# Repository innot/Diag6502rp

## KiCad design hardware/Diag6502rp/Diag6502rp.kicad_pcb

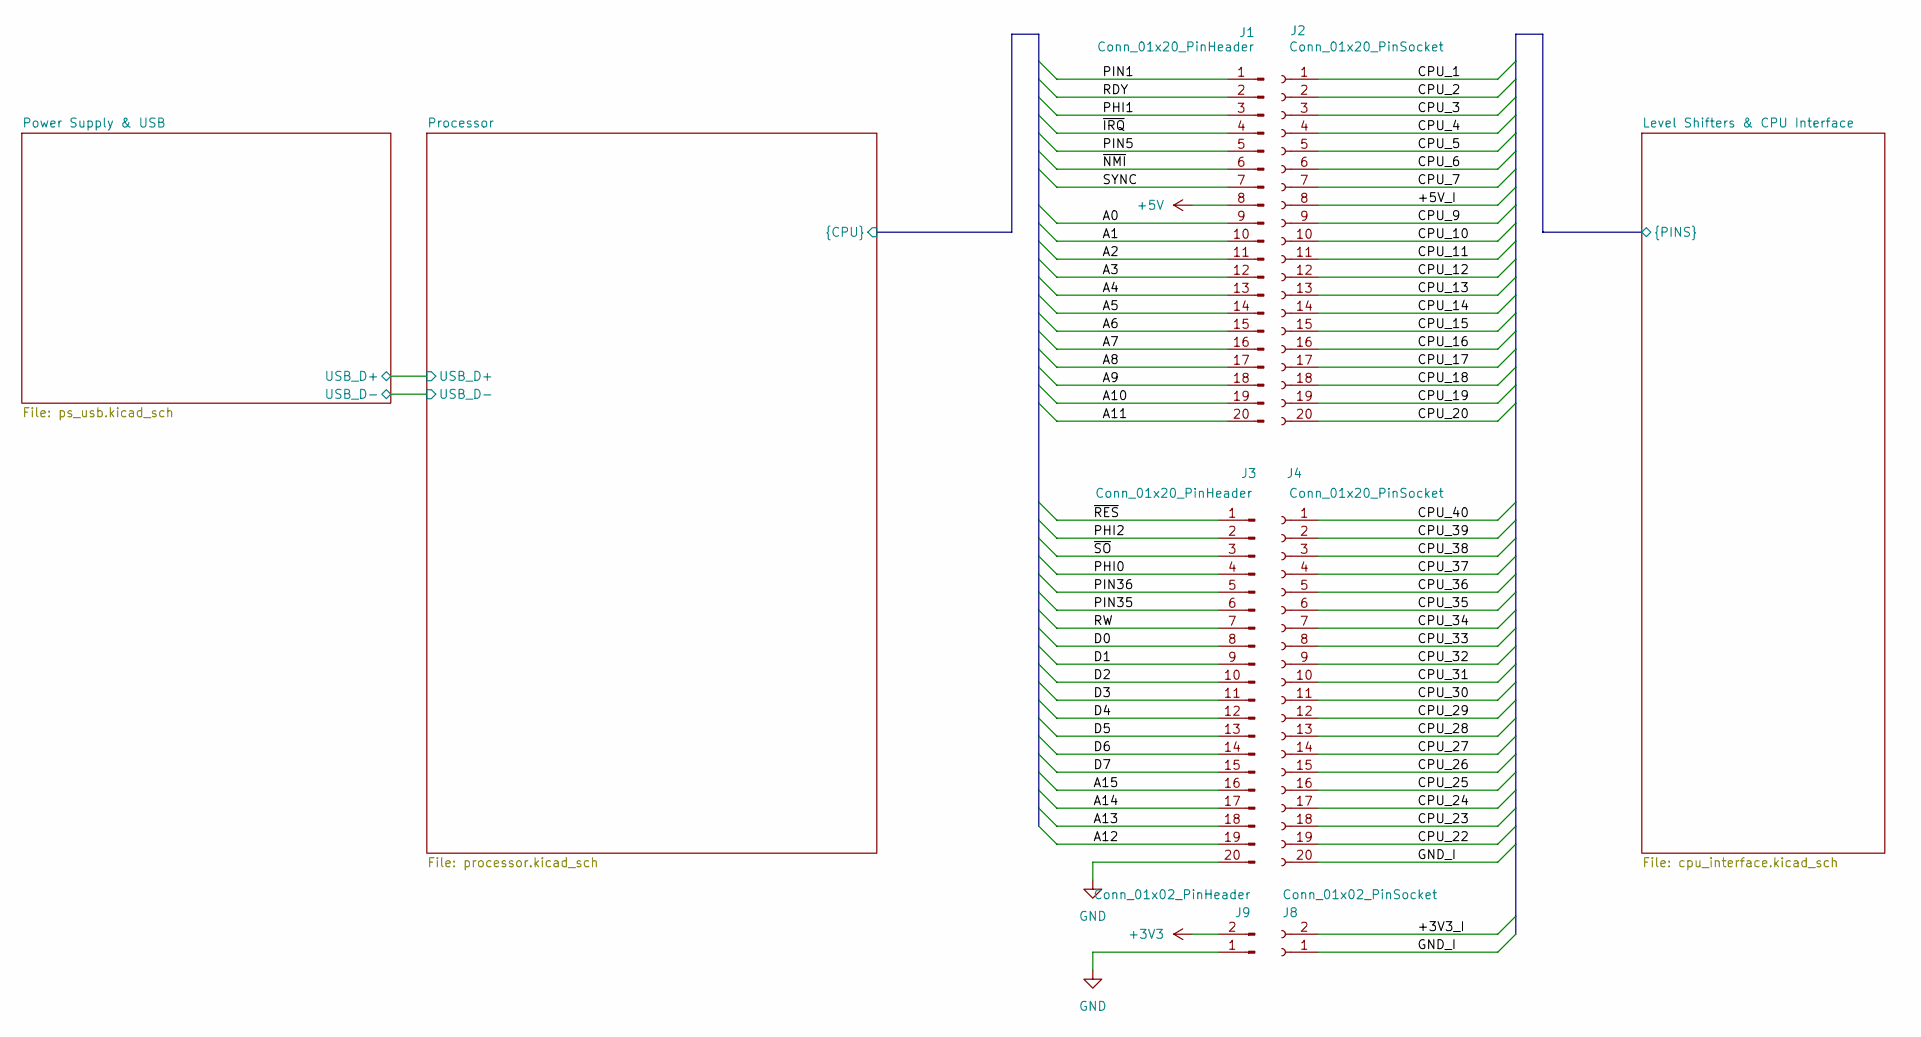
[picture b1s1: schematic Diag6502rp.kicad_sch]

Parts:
J1, J3: Conn_01x20_PinHeader; PinHeader_1x20_P2.54mm_Vertical; LCSC Part # C50981
J2, J4: Conn_01x20_PinSocket; PinSocket_1x20_P2.54mm_Vertical; LCSC Part # C7499336
J8: Conn_01x02_PinSocket; PinSocket_1x02_P2.54mm_Vertical; LCSC Part # C7499322
J9: Conn_01x02_PinHeader; PinHeader_1x02_P2.54mm_Vertical; LCSC Part # C492401

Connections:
+3V3: J9.2; also elsewhere on the board
+5V: J1.8; also elsewhere on the board
/Level Shifters & CPU Interface/+3V3_I: J8.2; also elsewhere on the board
/Level Shifters & CPU Interface/+5V_I: J2.8; also elsewhere on the board
/Level Shifters & CPU Interface/CPU_1: J2.1; also elsewhere on the board
/Level Shifters & CPU Interface/CPU_2: J2.2; also elsewhere on the board
/Level Shifters & CPU Interface/CPU_3: J2.3; also elsewhere on the board
/Level Shifters & CPU Interface/CPU_4: J2.4; also elsewhere on the board
/Level Shifters & CPU Interface/CPU_5: J2.5; also elsewhere on the board
/Level Shifters & CPU Interface/CPU_6: J2.6; also elsewhere on the board
/Level Shifters & CPU Interface/CPU_7: J2.7; also elsewhere on the board
/Level Shifters & CPU Interface/CPU_9: J2.9; also elsewhere on the board
/Level Shifters & CPU Interface/CPU_10: J2.10; also elsewhere on the board
/Level Shifters & CPU Interface/CPU_11: J2.11; also elsewhere on the board
/Level Shifters & CPU Interface/CPU_12: J2.12; also elsewhere on the board
/Level Shifters & CPU Interface/CPU_13: J2.13; also elsewhere on the board
/Level Shifters & CPU Interface/CPU_14: J2.14; also elsewhere on the board
/Level Shifters & CPU Interface/CPU_15: J2.15; also elsewhere on the board
/Level Shifters & CPU Interface/CPU_16: J2.16; also elsewhere on the board
/Level Shifters & CPU Interface/CPU_17: J2.17; also elsewhere on the board
/Level Shifters & CPU Interface/CPU_18: J2.18; also elsewhere on the board
/Level Shifters & CPU Interface/CPU_19: J2.19; also elsewhere on the board
/Level Shifters & CPU Interface/CPU_20: J2.20; also elsewhere on the board
/Level Shifters & CPU Interface/CPU_22: J4.19; also elsewhere on the board
/Level Shifters & CPU Interface/CPU_23: J4.18; also elsewhere on the board
/Level Shifters & CPU Interface/CPU_24: J4.17; also elsewhere on the board
/Level Shifters & CPU Interface/CPU_25: J4.16; also elsewhere on the board
/Level Shifters & CPU Interface/CPU_26: J4.15; also elsewhere on the board
/Level Shifters & CPU Interface/CPU_27: J4.14; also elsewhere on the board
/Level Shifters & CPU Interface/CPU_28: J4.13; also elsewhere on the board
/Level Shifters & CPU Interface/CPU_29: J4.12; also elsewhere on the board
/Level Shifters & CPU Interface/CPU_30: J4.11; also elsewhere on the board
/Level Shifters & CPU Interface/CPU_31: J4.10; also elsewhere on the board
/Level Shifters & CPU Interface/CPU_32: J4.9; also elsewhere on the board
/Level Shifters & CPU Interface/CPU_33: J4.8; also elsewhere on the board
/Level Shifters & CPU Interface/CPU_34: J4.7; also elsewhere on the board
/Level Shifters & CPU Interface/CPU_35: J4.6; also elsewhere on the board
/Level Shifters & CPU Interface/CPU_36: J4.5; also elsewhere on the board
/Level Shifters & CPU Interface/CPU_37: J4.4; also elsewhere on the board
/Level Shifters & CPU Interface/CPU_38: J4.3; also elsewhere on the board
/Level Shifters & CPU Interface/CPU_39: J4.2; also elsewhere on the board
/Level Shifters & CPU Interface/CPU_40: J4.1; also elsewhere on the board
/Level Shifters & CPU Interface/GND_I: J4.20, J8.1; also elsewhere on the board
/Processor/A0: J1.9; also elsewhere on the board
/Processor/A1: J1.10; also elsewhere on the board
/Processor/A2: J1.11; also elsewhere on the board
/Processor/A3: J1.12; also elsewhere on the board
/Processor/A4: J1.13; also elsewhere on the board
/Processor/A5: J1.14; also elsewhere on the board
/Processor/A6: J1.15; also elsewhere on the board
/Processor/A7: J1.16; also elsewhere on the board
/Processor/A8: J1.17; also elsewhere on the board
/Processor/A9: J1.18; also elsewhere on the board
/Processor/A10: J1.19; also elsewhere on the board
/Processor/A11: J1.20; also elsewhere on the board
/Processor/A12: J3.19; also elsewhere on the board
/Processor/A13: J3.18; also elsewhere on the board
/Processor/A14: J3.17; also elsewhere on the board
/Processor/A15: J3.16; also elsewhere on the board
/Processor/D0: J3.8; also elsewhere on the board
/Processor/D1: J3.9; also elsewhere on the board
/Processor/D2: J3.10; also elsewhere on the board
/Processor/D3: J3.11; also elsewhere on the board
/Processor/D4: J3.12; also elsewhere on the board
/Processor/D5: J3.13; also elsewhere on the board
/Processor/D6: J3.14; also elsewhere on the board
/Processor/D7: J3.15; also elsewhere on the board
/Processor/PHI0: J3.4; also elsewhere on the board
/Processor/PHI1: J1.3; also elsewhere on the board
/Processor/PHI2: J3.2; also elsewhere on the board
/Processor/PIN1: J1.1; also elsewhere on the board
/Processor/PIN5: J1.5; also elsewhere on the board
/Processor/PIN35: J3.6; also elsewhere on the board
/Processor/PIN36: J3.5; also elsewhere on the board
/Processor/RDY: J1.2; also elsewhere on the board
/Processor/RW: J3.7; also elsewhere on the board
/Processor/SYNC: J1.7; also elsewhere on the board
/Processor/~IRQ: J1.4; also elsewhere on the board
/Processor/~NMI: J1.6; also elsewhere on the board
/Processor/~RES: J3.1; also elsewhere on the board
/Processor/~SO: J3.3; also elsewhere on the board
GND: J3.20, J9.1; also elsewhere on the board

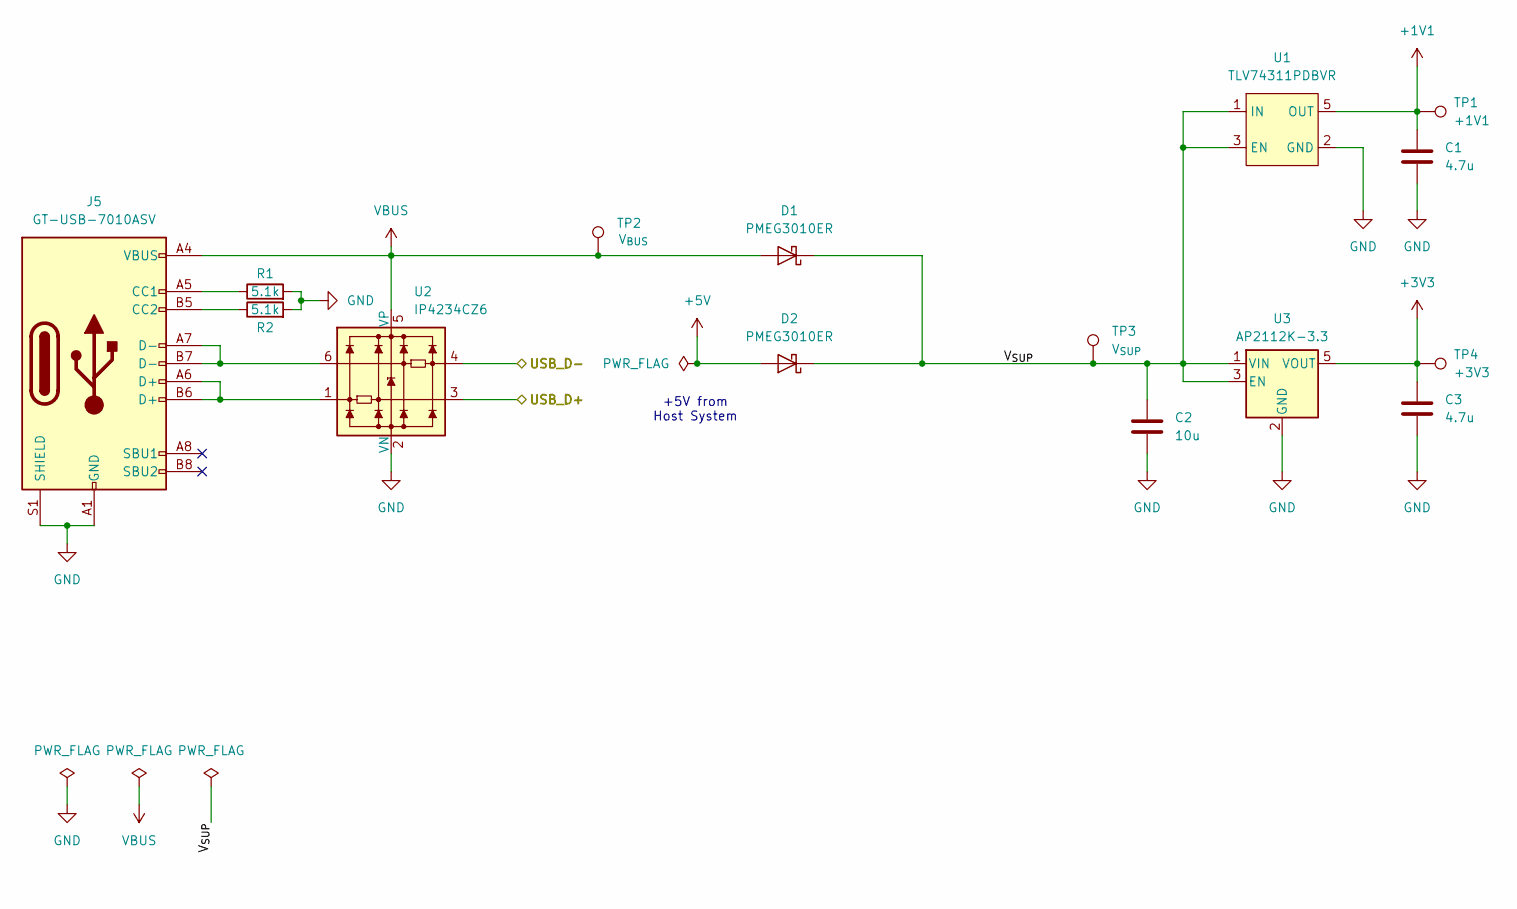
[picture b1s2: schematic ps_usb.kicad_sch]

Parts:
C1, C3: 4.7u; C_0402_1005Metric; LCSC Part # C23733
C2: 10u; C_0603_1608Metric; LCSC Part # C19702
D1, D2: PMEG3010ER; Nexperia_CFP3_SOD-123W; LCSC Part # C456106
J5: GT-USB-7010ASV; USB_C_Receptacle_G-Switch_GT-USB-7010ASV
R1, R2: 5.1k; R_0402_1005Metric; LCSC Part # C25905
TP1: +1V1; TestPoint_Pad_1.0x1.0mm
TP2: V_{BUS}; TestPoint_Pad_1.0x1.0mm
TP3: V_{SUP}; TestPoint_Pad_1.0x1.0mm
TP4: +3V3; TestPoint_Pad_1.0x1.0mm
U1: TLV74311PDBVR; SOT-23-5; LCSC Part # C485147
U2: IP4234CZ6; SC-74-6_1.55x2.9mm_P0.95mm; LCSC Part # C455086
U3: AP2112K-3.3; SOT-23-5; LCSC Part # C51118

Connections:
+1V1: C1.1, TP1.1, U1.5 (OUT); also elsewhere on the board
+3V3: C3.1, TP4.1, U3.5 (VOUT); also elsewhere on the board
+5V: D2.2 (A); also elsewhere on the board
/Power Supply & USB/V_{SUP}: C2.1, D1.1 (K), D2.1 (K), TP3.1, U1.1 (IN), U1.3 (EN), U3.1 (VIN), U3.3 (EN)
/Processor/USB_D+: U2.3; also elsewhere on the board
/Processor/USB_D-: U2.4; also elsewhere on the board
GND: C1.2, C2.2, C3.2, J5.A1 (GND), J5.A12 (GND), J5.B1 (GND), J5.B12 (GND), J5.S1 (SHIELD), R1.2, R2.2, U1.2 (GND), U2.2 (VN), U3.2 (GND); also elsewhere on the board
unnamed: J5.A5 (CC1), R1.1
unnamed: J5.B5 (CC2), R2.1
unnamed: J5.A6 (D+), J5.B6 (D+), U2.1
unnamed: J5.A7 (D-), J5.B7 (D-), U2.6
VBUS: D1.2 (A), J5.A4 (VBUS), J5.A9 (VBUS), J5.B4 (VBUS), J5.B9 (VBUS), TP2.1, U2.5 (VP)

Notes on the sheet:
+5V from Host System

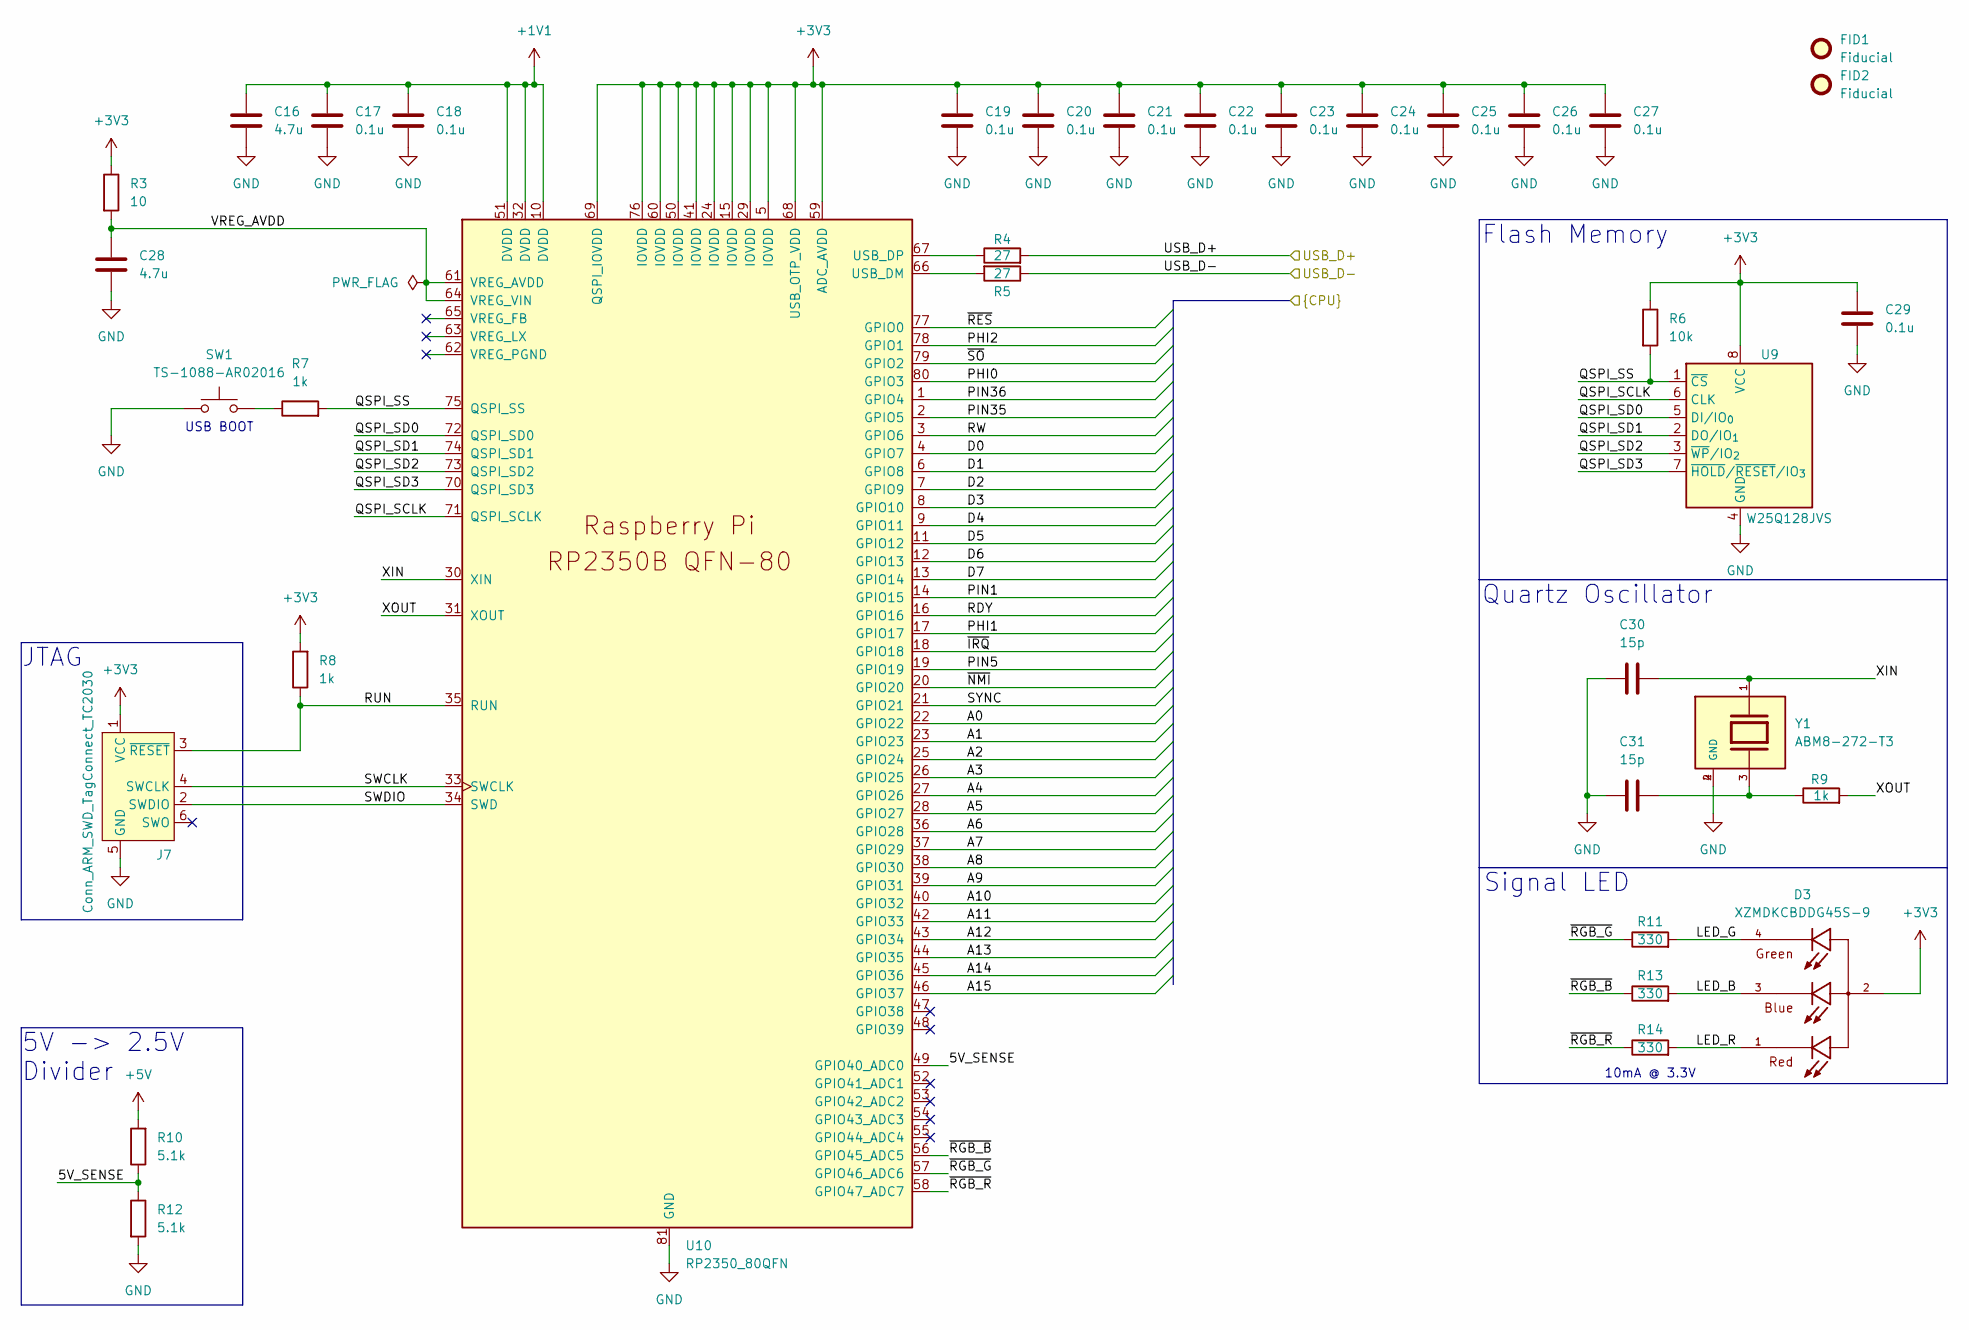
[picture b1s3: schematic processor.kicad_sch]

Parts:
C16, C28: 4.7u; C_0402_1005Metric; LCSC Part # C23733
C17, C18, C19, C20, C21, C22, C23, C24, C25, C26, C27, C29: 0.1u; C_0402_1005Metric; LCSC Part # C1525
C30, C31: 15p; C_0402_1005Metric; LCSC Part # C1548
D3: XZMDKCBDDG45S-9; LED_XZMDKCBDDG45S-9; PARTREV V11-Z; DigiKey_Part_Number 1497-1257-2-ND
FID1, FID2: Fiducial; Fiducial_1mm_Mask2mm
J7: Conn_ARM_SWD_TagConnect_TC2030; Tag-Connect_TC2030-IDC-FP_2x03_P1.27mm_Vertical
R3: 10; R_0402_1005Metric; LCSC Part # C25077
R4, R5: 27; R_0402_1005Metric; LCSC Part # C138021
R6: 10k; R_0402_1005Metric; LCSC Part # C25744
R7, R8, R9: 1k; R_0402_1005Metric; LCSC Part # C11702
R10, R12: 5.1k; R_0402_1005Metric; LCSC Part # C25905
R11, R13, R14: 330; R_0402_1005Metric; LCSC Part # C25130
SW1: TS-1088-AR02016; TS-1088-xxxxxxx; LCSC Part # C720477
U9: W25Q128JVS; SOIC-8_5.3x5.3mm_P1.27mm; LCSC Part # C97521
U10: RP2350_80QFN; RP2350-QFN-80-1EP_10x10_P0.4mm_EP3.4x3.4mm_ThermalVias; LCSC Part # C42415655
Y1: ABM8-272-T3; XTAL_ABM8-272-T3; PARTREV 07-29-20; LCSC Part # C20625731

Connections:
+1V1: C16.1, C17.1, C18.1, U10.10 (DVDD), U10.32 (DVDD), U10.51 (DVDD); also elsewhere on the board
+3V3: C19.1, C20.1, C21.1, C22.1, C23.1, C24.1, C25.1, C26.1, C27.1, C29.1, D3.2, J7.1 (VCC), R3.1, R6.1, R8.2, U9.8 (VCC), U10.5 (IOVDD), U10.15 (IOVDD), U10.24 (IOVDD), U10.29 (IOVDD), U10.41 (IOVDD), U10.50 (IOVDD), U10.59 (ADC_AVDD), U10.60 (IOVDD), U10.68 (USB_OTP_VDD), U10.69 (QSPI_IOVDD), U10.76 (IOVDD); also elsewhere on the board
+5V: R10.2; also elsewhere on the board
/Processor/5V_SENSE: R10.1, R12.1, U10.49 (GPIO40_ADC0)
/Processor/A0: U10.22 (GPIO22); also elsewhere on the board
/Processor/A1: U10.23 (GPIO23); also elsewhere on the board
/Processor/A2: U10.25 (GPIO24); also elsewhere on the board
/Processor/A3: U10.26 (GPIO25); also elsewhere on the board
/Processor/A4: U10.27 (GPIO26); also elsewhere on the board
/Processor/A5: U10.28 (GPIO27); also elsewhere on the board
/Processor/A6: U10.36 (GPIO28); also elsewhere on the board
/Processor/A7: U10.37 (GPIO29); also elsewhere on the board
/Processor/A8: U10.38 (GPIO30); also elsewhere on the board
/Processor/A9: U10.39 (GPIO31); also elsewhere on the board
/Processor/A10: U10.40 (GPIO32); also elsewhere on the board
/Processor/A11: U10.42 (GPIO33); also elsewhere on the board
/Processor/A12: U10.43 (GPIO34); also elsewhere on the board
/Processor/A13: U10.44 (GPIO35); also elsewhere on the board
/Processor/A14: U10.45 (GPIO36); also elsewhere on the board
/Processor/A15: U10.46 (GPIO37); also elsewhere on the board
/Processor/D0: U10.4 (GPIO7); also elsewhere on the board
/Processor/D1: U10.6 (GPIO8); also elsewhere on the board
/Processor/D2: U10.7 (GPIO9); also elsewhere on the board
/Processor/D3: U10.8 (GPIO10); also elsewhere on the board
/Processor/D4: U10.9 (GPIO11); also elsewhere on the board
/Processor/D5: U10.11 (GPIO12); also elsewhere on the board
/Processor/D6: U10.12 (GPIO13); also elsewhere on the board
/Processor/D7: U10.13 (GPIO14); also elsewhere on the board
/Processor/LED_B: D3.3, R13.2
/Processor/LED_G: D3.4, R11.2
/Processor/LED_R: D3.1, R14.2
/Processor/PHI0: U10.80 (GPIO3); also elsewhere on the board
/Processor/PHI1: U10.17 (GPIO17); also elsewhere on the board
/Processor/PHI2: U10.78 (GPIO1); also elsewhere on the board
/Processor/PIN1: U10.14 (GPIO15); also elsewhere on the board
/Processor/PIN5: U10.19 (GPIO19); also elsewhere on the board
/Processor/PIN35: U10.2 (GPIO5); also elsewhere on the board
/Processor/PIN36: U10.1 (GPIO4); also elsewhere on the board
/Processor/QSPI_SCLK: U9.6 (CLK), U10.71 (QSPI_SCLK)
/Processor/QSPI_SD0: U9.5 (DI/IO_{0}), U10.72 (QSPI_SD0)
/Processor/QSPI_SD1: U9.2 (DO/IO_{1}), U10.74 (QSPI_SD1)
/Processor/QSPI_SD2: U9.3 (~WP/IO_{2}), U10.73 (QSPI_SD2)
/Processor/QSPI_SD3: U9.7 (~HOLD/~RESET/IO_{3}), U10.70 (QSPI_SD3)
/Processor/QSPI_SS: R6.2, R7.2, U9.1 (~CS), U10.75 (QSPI_SS)
/Processor/RDY: U10.16 (GPIO16); also elsewhere on the board
/Processor/RUN: J7.3 (~RESET), R8.1, U10.35 (RUN)
/Processor/RW: U10.3 (GPIO6); also elsewhere on the board
/Processor/SWCLK: J7.4 (SWCLK), U10.33 (SWCLK)
/Processor/SWDIO: J7.2 (SWDIO), U10.34 (SWD)
/Processor/SYNC: U10.21 (GPIO21); also elsewhere on the board
/Processor/USB_D+: R4.2; also elsewhere on the board
/Processor/USB_D-: R5.1; also elsewhere on the board
/Processor/VREG_AVDD: C28.1, R3.2, U10.61 (VREG_AVDD), U10.64 (VREG_VIN)
/Processor/XIN: C30.2, U10.30 (XIN), Y1.1
/Processor/XOUT: R9.2, U10.31 (XOUT)
/Processor/~IRQ: U10.18 (GPIO18); also elsewhere on the board
/Processor/~NMI: U10.20 (GPIO20); also elsewhere on the board
/Processor/~RES: U10.77 (GPIO0); also elsewhere on the board
/Processor/~RGB_B: R13.1, U10.56 (GPIO45_ADC5)
/Processor/~RGB_G: R11.1, U10.57 (GPIO46_ADC6)
/Processor/~RGB_R: R14.1, U10.58 (GPIO47_ADC7)
/Processor/~SO: U10.79 (GPIO2); also elsewhere on the board
GND: C16.2, C17.2, C18.2, C19.2, C20.2, C21.2, C22.2, C23.2, C24.2, C25.2, C26.2, C27.2, C28.2, C29.2, C30.1, C31.1, J7.5 (GND), R12.2, SW1.1, U9.4 (GND), U10.81 (GND), Y1.2 (GND), Y1.4 (GND); also elsewhere on the board
unnamed: C31.2, R9.1, Y1.3
unnamed: R7.1, SW1.2
unnamed: R5.2, U10.66 (USB_DM)
unnamed: R4.1, U10.67 (USB_DP)

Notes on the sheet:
10mA @ 3.3V
5V -> 2.5V Divider
USB BOOT
Signal LED
JTAG
Quartz Oscillator
Flash Memory

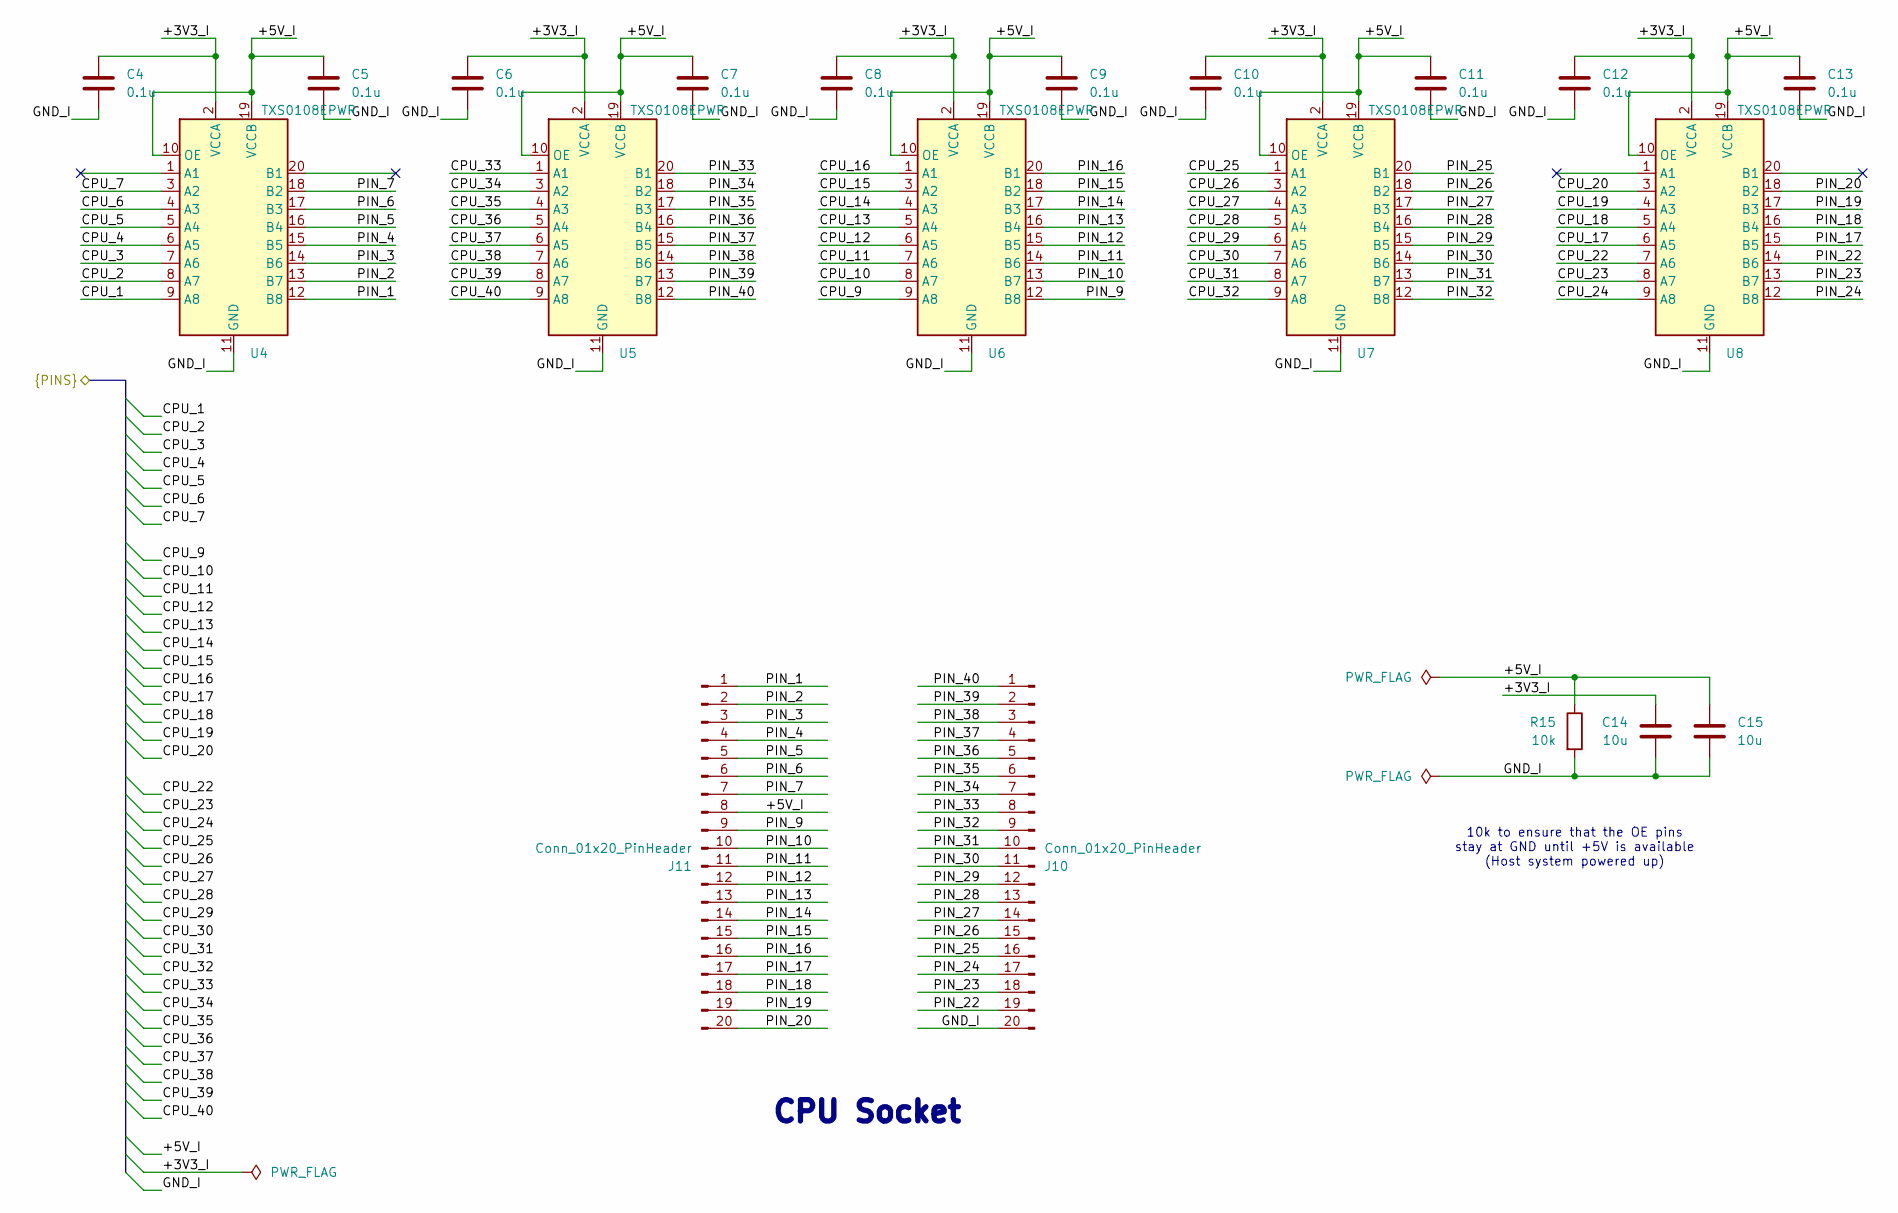
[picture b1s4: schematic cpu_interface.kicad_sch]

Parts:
C4, C5, C6, C7, C8, C9, C10, C11, C12, C13: 0.1u; C_0402_1005Metric; LCSC Part # C1525
C14, C15: 10u; C_0603_1608Metric; LCSC Part # C19702
J10, J11: Conn_01x20_PinHeader; PinHeader_1x20_P2.54mm_Vertical; LCSC Part # C50981
R15: 10k; R_0402_1005Metric; LCSC Part # C25744
U4, U5, U6, U7, U8: TXS0108EPWR; TSSOP-20_4.4x6.5mm_P0.65mm; LCSC Part # C17206

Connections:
/Level Shifters & CPU Interface/+3V3_I: C4.1, C6.1, C8.1, C10.1, C12.1, C14.1, U4.2 (VCCA), U5.2 (VCCA), U6.2 (VCCA), U7.2 (VCCA), U8.2 (VCCA); also elsewhere on the board
/Level Shifters & CPU Interface/+5V_I: C5.1, C7.1, C9.1, C11.1, C13.1, C15.1, J11.8, R15.1, U4.10 (OE), U4.19 (VCCB), U5.10 (OE), U5.19 (VCCB), U6.10 (OE), U6.19 (VCCB), U7.10 (OE), U7.19 (VCCB), U8.10 (OE), U8.19 (VCCB); also elsewhere on the board
/Level Shifters & CPU Interface/CPU_1: U4.9 (A8); also elsewhere on the board
/Level Shifters & CPU Interface/CPU_2: U4.8 (A7); also elsewhere on the board
/Level Shifters & CPU Interface/CPU_3: U4.7 (A6); also elsewhere on the board
/Level Shifters & CPU Interface/CPU_4: U4.6 (A5); also elsewhere on the board
/Level Shifters & CPU Interface/CPU_5: U4.5 (A4); also elsewhere on the board
/Level Shifters & CPU Interface/CPU_6: U4.4 (A3); also elsewhere on the board
/Level Shifters & CPU Interface/CPU_7: U4.3 (A2); also elsewhere on the board
/Level Shifters & CPU Interface/CPU_9: U6.9 (A8); also elsewhere on the board
/Level Shifters & CPU Interface/CPU_10: U6.8 (A7); also elsewhere on the board
/Level Shifters & CPU Interface/CPU_11: U6.7 (A6); also elsewhere on the board
/Level Shifters & CPU Interface/CPU_12: U6.6 (A5); also elsewhere on the board
/Level Shifters & CPU Interface/CPU_13: U6.5 (A4); also elsewhere on the board
/Level Shifters & CPU Interface/CPU_14: U6.4 (A3); also elsewhere on the board
/Level Shifters & CPU Interface/CPU_15: U6.3 (A2); also elsewhere on the board
/Level Shifters & CPU Interface/CPU_16: U6.1 (A1); also elsewhere on the board
/Level Shifters & CPU Interface/CPU_17: U8.6 (A5); also elsewhere on the board
/Level Shifters & CPU Interface/CPU_18: U8.5 (A4); also elsewhere on the board
/Level Shifters & CPU Interface/CPU_19: U8.4 (A3); also elsewhere on the board
/Level Shifters & CPU Interface/CPU_20: U8.3 (A2); also elsewhere on the board
/Level Shifters & CPU Interface/CPU_22: U8.7 (A6); also elsewhere on the board
/Level Shifters & CPU Interface/CPU_23: U8.8 (A7); also elsewhere on the board
/Level Shifters & CPU Interface/CPU_24: U8.9 (A8); also elsewhere on the board
/Level Shifters & CPU Interface/CPU_25: U7.1 (A1); also elsewhere on the board
/Level Shifters & CPU Interface/CPU_26: U7.3 (A2); also elsewhere on the board
/Level Shifters & CPU Interface/CPU_27: U7.4 (A3); also elsewhere on the board
/Level Shifters & CPU Interface/CPU_28: U7.5 (A4); also elsewhere on the board
/Level Shifters & CPU Interface/CPU_29: U7.6 (A5); also elsewhere on the board
/Level Shifters & CPU Interface/CPU_30: U7.7 (A6); also elsewhere on the board
/Level Shifters & CPU Interface/CPU_31: U7.8 (A7); also elsewhere on the board
/Level Shifters & CPU Interface/CPU_32: U7.9 (A8); also elsewhere on the board
/Level Shifters & CPU Interface/CPU_33: U5.1 (A1); also elsewhere on the board
/Level Shifters & CPU Interface/CPU_34: U5.3 (A2); also elsewhere on the board
/Level Shifters & CPU Interface/CPU_35: U5.4 (A3); also elsewhere on the board
/Level Shifters & CPU Interface/CPU_36: U5.5 (A4); also elsewhere on the board
/Level Shifters & CPU Interface/CPU_37: U5.6 (A5); also elsewhere on the board
/Level Shifters & CPU Interface/CPU_38: U5.7 (A6); also elsewhere on the board
/Level Shifters & CPU Interface/CPU_39: U5.8 (A7); also elsewhere on the board
/Level Shifters & CPU Interface/CPU_40: U5.9 (A8); also elsewhere on the board
/Level Shifters & CPU Interface/GND_I: C4.2, C5.2, C6.2, C7.2, C8.2, C9.2, C10.2, C11.2, C12.2, C13.2, C14.2, C15.2, J10.20, R15.2, U4.11 (GND), U5.11 (GND), U6.11 (GND), U7.11 (GND), U8.11 (GND); also elsewhere on the board
/Level Shifters & CPU Interface/PIN_1: J11.1, U4.12 (B8)
/Level Shifters & CPU Interface/PIN_2: J11.2, U4.13 (B7)
/Level Shifters & CPU Interface/PIN_3: J11.3, U4.14 (B6)
/Level Shifters & CPU Interface/PIN_4: J11.4, U4.15 (B5)
/Level Shifters & CPU Interface/PIN_5: J11.5, U4.16 (B4)
/Level Shifters & CPU Interface/PIN_6: J11.6, U4.17 (B3)
/Level Shifters & CPU Interface/PIN_7: J11.7, U4.18 (B2)
/Level Shifters & CPU Interface/PIN_9: J11.9, U6.12 (B8)
/Level Shifters & CPU Interface/PIN_10: J11.10, U6.13 (B7)
/Level Shifters & CPU Interface/PIN_11: J11.11, U6.14 (B6)
/Level Shifters & CPU Interface/PIN_12: J11.12, U6.15 (B5)
/Level Shifters & CPU Interface/PIN_13: J11.13, U6.16 (B4)
/Level Shifters & CPU Interface/PIN_14: J11.14, U6.17 (B3)
/Level Shifters & CPU Interface/PIN_15: J11.15, U6.18 (B2)
/Level Shifters & CPU Interface/PIN_16: J11.16, U6.20 (B1)
/Level Shifters & CPU Interface/PIN_17: J11.17, U8.15 (B5)
/Level Shifters & CPU Interface/PIN_18: J11.18, U8.16 (B4)
/Level Shifters & CPU Interface/PIN_19: J11.19, U8.17 (B3)
/Level Shifters & CPU Interface/PIN_20: J11.20, U8.18 (B2)
/Level Shifters & CPU Interface/PIN_22: J10.19, U8.14 (B6)
/Level Shifters & CPU Interface/PIN_23: J10.18, U8.13 (B7)
/Level Shifters & CPU Interface/PIN_24: J10.17, U8.12 (B8)
/Level Shifters & CPU Interface/PIN_25: J10.16, U7.20 (B1)
/Level Shifters & CPU Interface/PIN_26: J10.15, U7.18 (B2)
/Level Shifters & CPU Interface/PIN_27: J10.14, U7.17 (B3)
/Level Shifters & CPU Interface/PIN_28: J10.13, U7.16 (B4)
/Level Shifters & CPU Interface/PIN_29: J10.12, U7.15 (B5)
/Level Shifters & CPU Interface/PIN_30: J10.11, U7.14 (B6)
/Level Shifters & CPU Interface/PIN_31: J10.10, U7.13 (B7)
/Level Shifters & CPU Interface/PIN_32: J10.9, U7.12 (B8)
/Level Shifters & CPU Interface/PIN_33: J10.8, U5.20 (B1)
/Level Shifters & CPU Interface/PIN_34: J10.7, U5.18 (B2)
/Level Shifters & CPU Interface/PIN_35: J10.6, U5.17 (B3)
/Level Shifters & CPU Interface/PIN_36: J10.5, U5.16 (B4)
/Level Shifters & CPU Interface/PIN_37: J10.4, U5.15 (B5)
/Level Shifters & CPU Interface/PIN_38: J10.3, U5.14 (B6)
/Level Shifters & CPU Interface/PIN_39: J10.2, U5.13 (B7)
/Level Shifters & CPU Interface/PIN_40: J10.1, U5.12 (B8)

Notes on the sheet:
10k to ensure that the OE pins stay at GND until +5V is available (Host system powered up)
CPU Socket

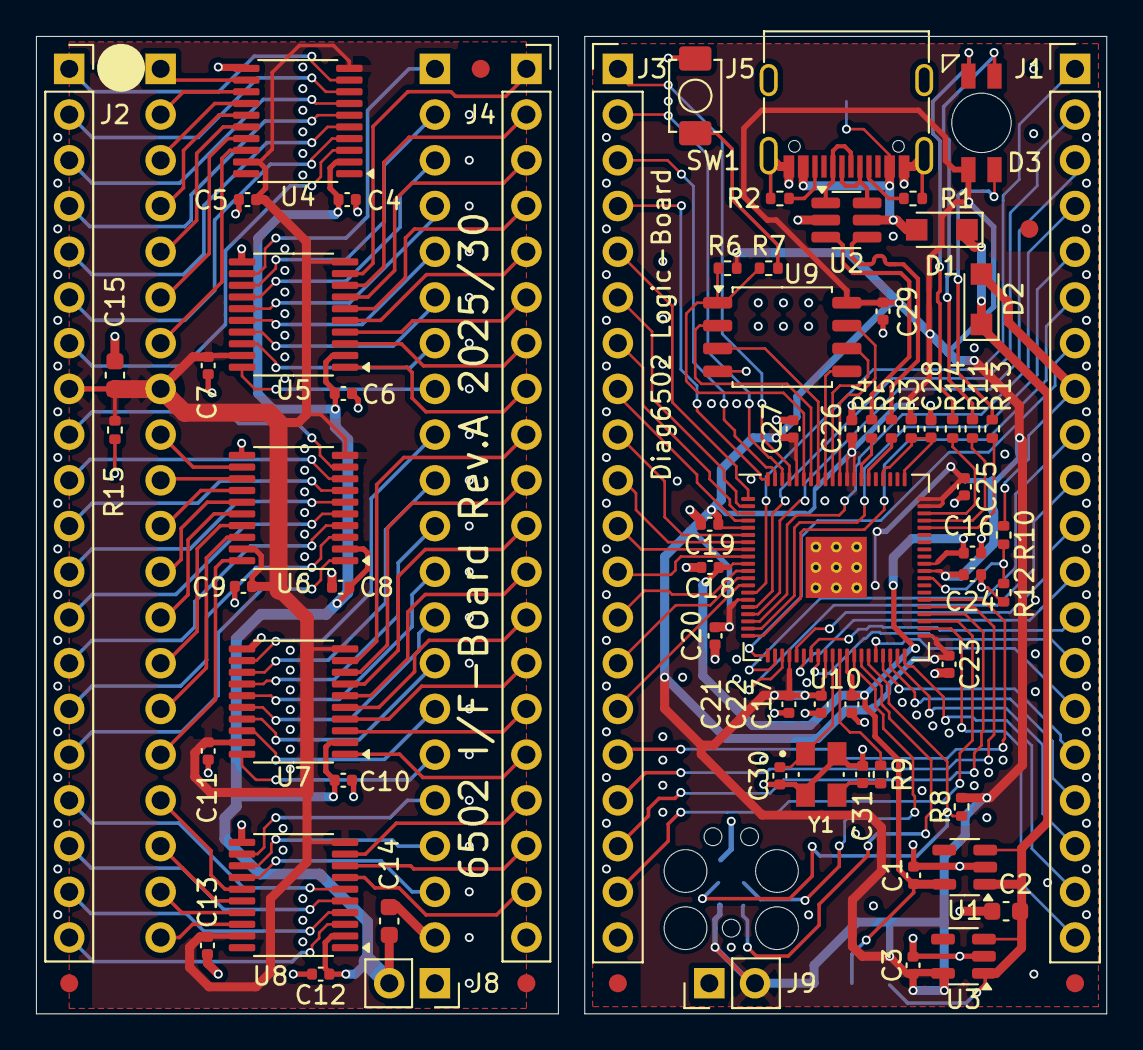
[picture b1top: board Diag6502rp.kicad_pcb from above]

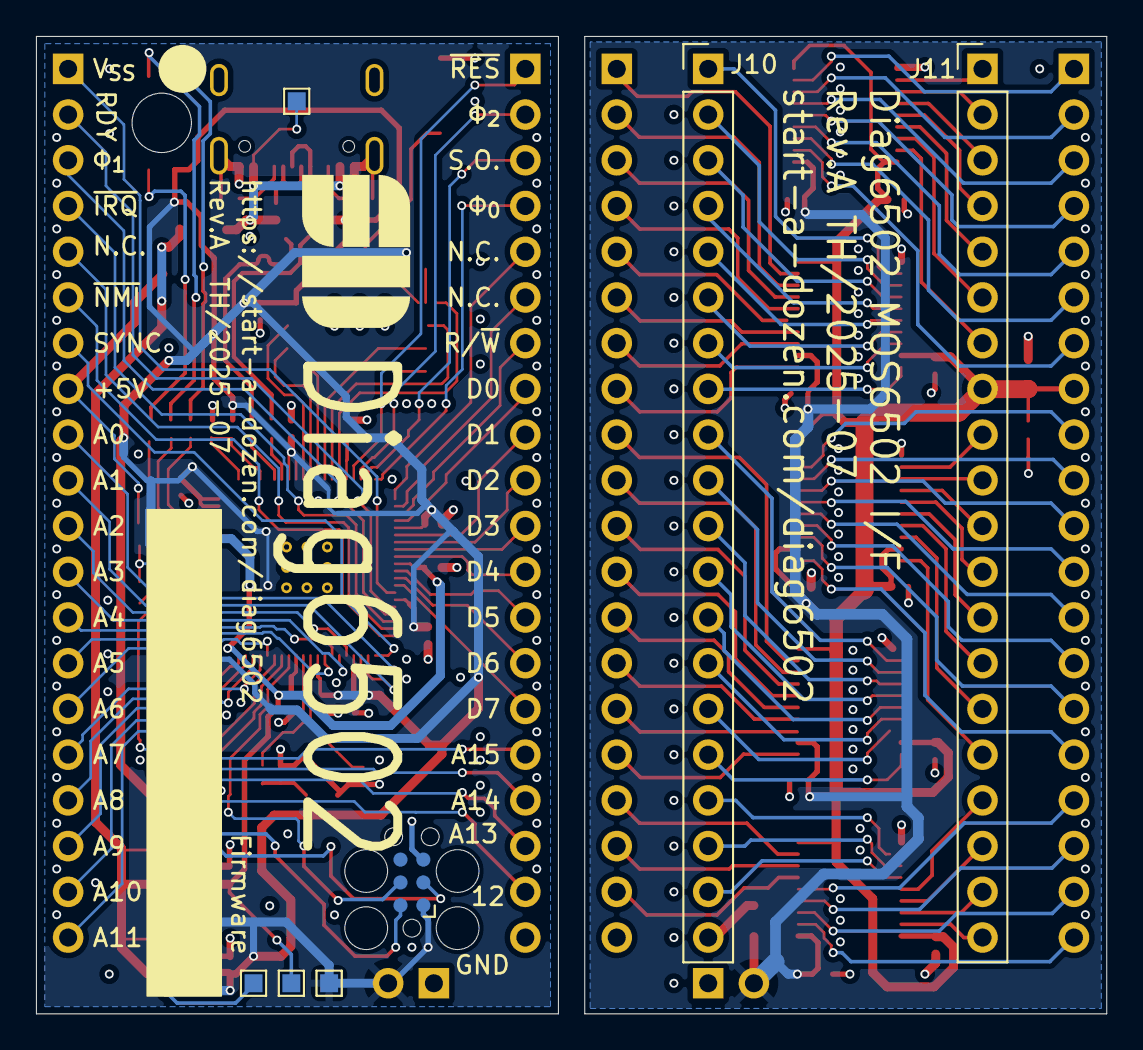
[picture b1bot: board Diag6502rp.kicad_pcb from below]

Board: 4 copper layers, 59.5 x 54.3 mm, 83 parts (7 on the bottom side), 152 nets.

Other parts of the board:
B1, B2: Board
FID3, FID4, FID5, FID6: Fiducial_1mm_Mask2mm

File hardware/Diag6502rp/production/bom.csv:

Designator,Footprint,Quantity,Value,LCSC Part #
"C1, C16, C28, C3",0402,4,4.7u,
"C10, C11, C12, C13, C17, C18, C19, C20, C21, C22, C23, C24, C25, C26, C27, C29, C4, C5, C6, C7, C8, C9",0402,22,0.1u,
"C14, C15, C2",0603,3,10u,
"C30, C31",0402,2,15p,
"D1, D2",Nexperia_CFP3_SOD-123W,2,PMEG3010ER,
D3,LED_XZMDKCBDDG45S-9,1,XZMDKCBDDG45S-9,
"J1, J3",PinHeader_1x20_P2.54mm_Vertical,2,Conn_01x20_PinHeader,
"J10, J11",PinHeader_1x20_P2.54mm_Vertical,2,Conn_01x20_Pin,
J2,PinSocket_1x20_P2.54mm_Vertical,1,Conn_01x21_PinSocket,
J4,PinSocket_1x20_P2.54mm_Vertical,1,Conn_01x20_PinSocket,
J5,GCT_USB4105-GF-A,1,USB4105-G-FA,
J8,PinSocket_1x02_P2.54mm_Vertical,1,Conn_01x02_Socket,
J9,PinHeader_1x02_P2.54mm_Vertical,1,Conn_01x02_Pin,
"R1, R10, R12, R2",0402,4,5.1k,
"R11, R13, R14",0402,3,680,
"R15, R6",0402,2,10k,
R3,0402,1,10,
"R4, R5",0402,2,27,
"R7, R8, R9",0402,3,1k,
SW1,SW_Push_1P1T_NO_CK_KMR2,1,SW_Push,
U1,SOT-23-5,1,TLV74311P,
U10,RP2350-QFN-80-1EP_10x10_P0.4mm_EP3.4x3.4mm_ThermalVias,1,RP2350_80QFN,
U2,SC-74-6_1.55x2.9mm_P0.95mm,1,IP4234CZ6,
U3,SOT-23-5,1,AP2112K-3.3,
"U4, U5, U6, U7, U8",TSSOP-20_4.4x6.5mm_P0.65mm,5,TXS0108EPW,
U9,SOIC-8_5.3x5.3mm_P1.27mm,1,W25Q128JVS,
Y1,XTAL_ABM8-272-T3,1,ABM8-272-T3,
